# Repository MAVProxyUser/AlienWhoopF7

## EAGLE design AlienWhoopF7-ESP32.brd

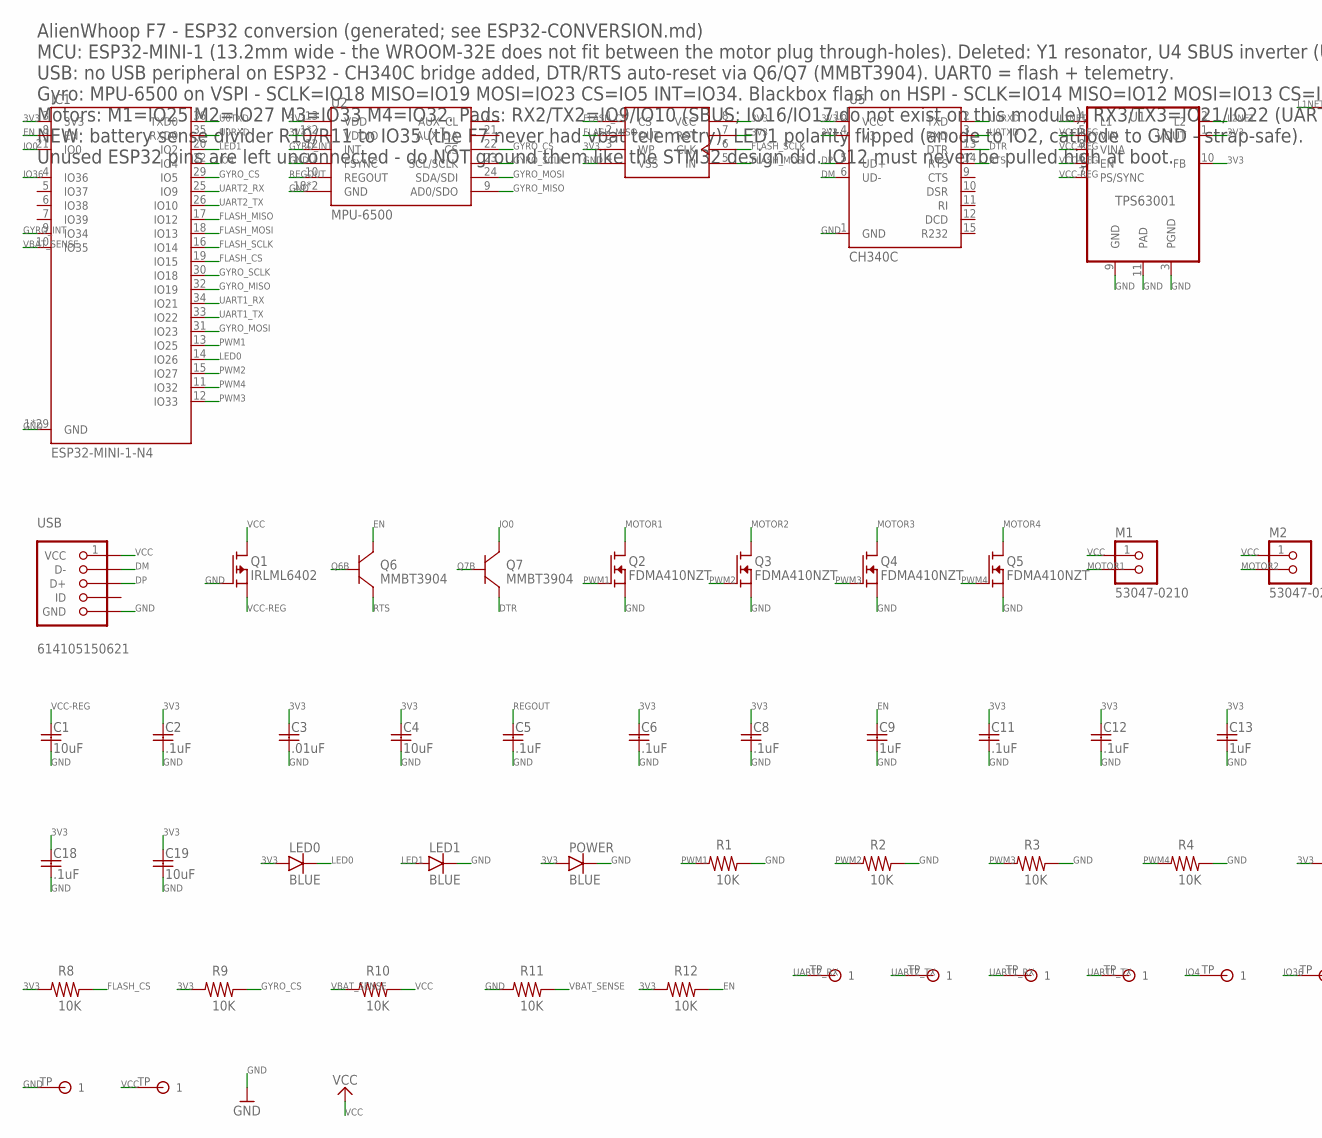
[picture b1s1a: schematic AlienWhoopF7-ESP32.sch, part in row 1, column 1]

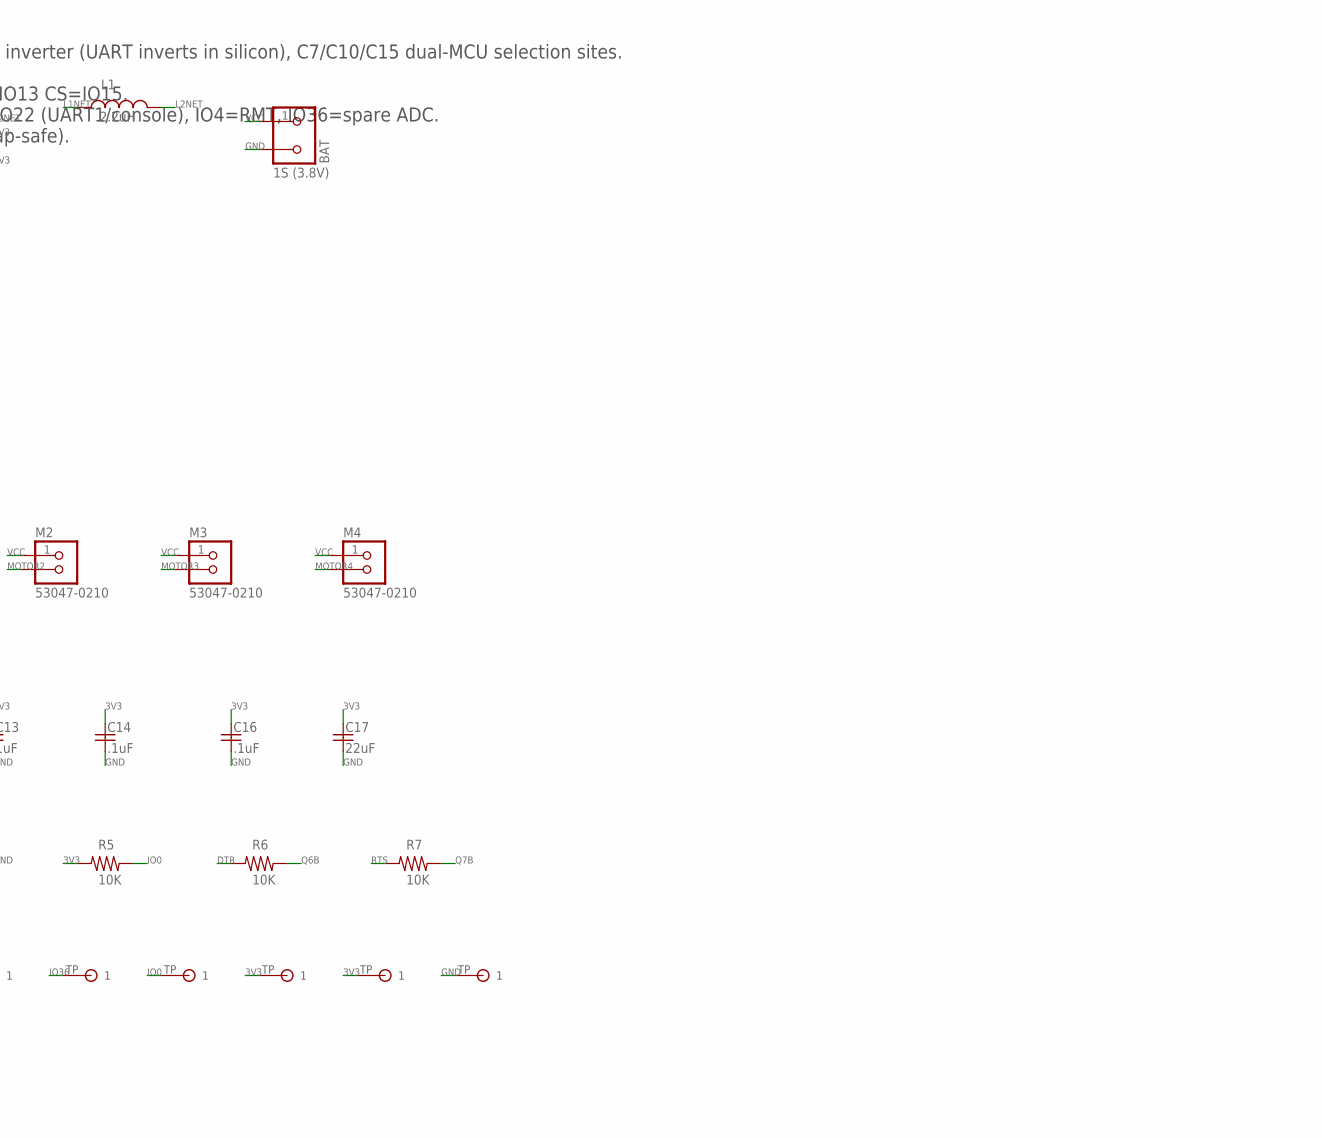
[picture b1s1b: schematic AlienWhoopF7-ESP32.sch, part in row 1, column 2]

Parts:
3.3V, 3V3: TESTPAD
BAT: 1S (3.8V); S2B-PH-K-S
BOOT: TESTPAD
C1, C4, C19: 10uF; YUDEN-CAP-0805
C2, C5, C6, C8, C11, C12, C14, C16, C18: .1uF; MUR-CAP-0603
C3: .01uF; MUR-CAP-0603
C9, C13: 1uF; MUR-CAP-0603
C17: 22uF; YUDEN-CAP-0805
GND: TESTPAD
GND@1: TESTPAD
IC1: ESP32-MINI-1-N4; ESP32-MINI-1
IO4, IO36: TESTPAD
L1: 2.2uH; DFE201612E-2R2M-P2
LED0, LED1: BLUE; SMD-CHIP-LED-0805
M1, M2, M3, M4: 53047-0210; PICO-53047-02
POWER: BLUE; SMD-CHIP-LED-0805
Q1: IRLML6402; SOT-23
Q2, Q3, Q4, Q5: FDMA410NZT; MICROFET-2X2
Q6, Q7: MMBT3904; SOT23
R1, R2, R3, R4, R5, R6, R7, R8, R9, R10, R11, R12: 10K; VISH-RES-0603
RX2, RX3: TESTPAD
TX2, TX3: TESTPAD
U1: TPS63001; VSON-N10
U2: MPU-6500; QFN24_PAD
U3: MX25L6406EM2I-12G; M25P32
U5: CH340C; SOP16
USB: 614105150621; USB-BFPV
VCC@1: TESTPAD

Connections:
3V3: 3.3V.TP, 3V3.TP, C2.1, C3.1, C4.1, C6.1, C8.1, C11.1, C12.1, C13.1, C14.1, C16.1, C17.1, C18.1, C19.1, IC1.3 (3V3), LED0.A, POWER.A, R5.2, R8.2, R9.2, R12.2, U1.1 (VOUT), U1.10 (FB), U2.1 (VDDIO), U2.8 (VDDIO), U2.13 (VDD), U3.3 (WP), U3.7 (RST), U3.8 (VCC), U5.4 (V3), U5.16 (VCC)
DM: U5.6 (UD-), USB.2 (D-)
DP: U5.5 (UD+), USB.3 (D+)
DTR: Q7.2 (E), R6.2, U5.13 (DTR)
EN: C9.1, IC1.8 (EN), Q6.3 (C), R12.1
FLASH_CS: IC1.19 (IO15), R8.1, U3.1 (CS)
FLASH_MISO: IC1.17 (IO12), U3.2 (OUT)
FLASH_MOSI: IC1.18 (IO13), U3.5 (IN)
FLASH_SCLK: IC1.16 (IO14), U3.6 (CLK)
GND: BAT.2, C1.2, C2.2, C3.2, C4.2, C5.2, C6.2, C8.2, C9.2, C11.2, C12.2, C13.2, C14.2, C16.2, C17.2, C18.2, C19.2, GND.TP, GND@1.TP, IC1.1 (GND), IC1.2 (GND), IC1.27 (GND), IC1.38 (GND), IC1.39 (GND), IC1.40 (GND), IC1.41 (GND), IC1.42 (GND), IC1.43 (GND), IC1.44 (GND), IC1.45 (GND), IC1.46 (GND), IC1.47 (GND), IC1.48 (GND), IC1.49 (GND), IC1.50 (GND), IC1.51 (GND), IC1.52 (GND), IC1.53 (GND), IC1.54 (GND), IC1.55 (GND), IC1.T1 (GND), IC1.T2 (GND), IC1.T3 (GND), IC1.T4 (GND), IC1.T5 (GND), IC1.T6 (GND), IC1.T7 (GND), IC1.T8 (GND), LED1.C, POWER.C, Q1.1 (G), Q2.S, Q2.S1 (S), Q3.S, Q3.S1 (S), Q4.S, Q4.S1 (S), Q5.S, Q5.S1 (S), R1.1, R2.1, R3.1, R4.1, R11.2, U1.3 (PGND), U1.9 (GND), U1.11 (PAD), U2.11 (FSYNC), U2.18 (GND), U2.20 (GND), U3.4 (VSS), U5.1 (GND), USB.5 (GND), USB.P$6 (GND), USB.P$7 (GND)
GYRO_CS: IC1.29 (IO5), R9.1, U2.22 (!CS)
GYRO_INT: IC1.9 (IO34), U2.12 (INT)
GYRO_MISO: IC1.32 (IO19), U2.9 (AD0/SDO)
GYRO_MOSI: IC1.31 (IO23), U2.24 (SDA/SDI)
GYRO_SCLK: IC1.30 (IO18), U2.23 (SCL/SCLK)
IO0: BOOT.TP, IC1.21 (IO0), Q7.3 (C), R5.1
IO4: IC1.22 (IO4), IO4.TP
IO36: IC1.4 (IO36), IO36.TP
L1NET: L1.P$1 (1), U1.4 (L1)
L2NET: L1.P$2 (2), U1.2 (L2)
LED0: IC1.14 (IO26), LED0.C
LED1: IC1.20 (IO2), LED1.A
MOTOR1: M1.2, Q2.D, Q2.D1 (D), Q2.D2 (D), Q2.D3 (D), Q2.D4 (D)
MOTOR2: M2.2, Q3.D, Q3.D1 (D), Q3.D2 (D), Q3.D3 (D), Q3.D4 (D)
MOTOR3: M3.2, Q4.D, Q4.D1 (D), Q4.D2 (D), Q4.D3 (D), Q4.D4 (D)
MOTOR4: M4.2, Q5.D, Q5.D1 (D), Q5.D2 (D), Q5.D3 (D), Q5.D4 (D)
PWM1: IC1.13 (IO25), Q2.G, R1.2
PWM2: IC1.15 (IO27), Q3.G, R2.2
PWM3: IC1.12 (IO33), Q4.G, R3.2
PWM4: IC1.11 (IO32), Q5.G, R4.2
Q6B: Q6.1 (B), R6.1
Q7B: Q7.1 (B), R7.1
REGOUT: C5.1, U2.10 (REGOUT)
RTS: Q6.2 (E), R7.2, U5.14 (RTS)
U0RXD: IC1.35 (RXD0), U5.2 (TXD)
U0TXD: IC1.36 (TXD0), U5.3 (RXD)
UART1_RX: IC1.34 (IO21), RX3.TP
UART1_TX: IC1.33 (IO22), TX3.TP
UART2_RX: IC1.25 (IO9), RX2.TP
UART2_TX: IC1.26 (IO10), TX2.TP
VBAT_SENSE: IC1.10 (IO35), R10.2, R11.1
VCC: BAT.1, M1.1, M2.1, M3.1, M4.1, Q1.3 (D), R10.1, USB.1 (VCC), VCC@1.TP
VCC-REG: C1.1, Q1.2 (S), U1.5 (VIN), U1.6 (EN), U1.7 (PS/SYNC), U1.8 (VINA)

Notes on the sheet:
AlienWhoop F7 - ESP32 conversion (generated; see ESP32-CONVERSION.md)
MCU: ESP32-MINI-1 (13.2mm wide - the WROOM-32E does not fit between the motor plug through-holes). Deleted: Y1 resonator, U4 SBUS inverter (UART inverts in silicon), C7/C10/C15 dual-MCU selection sites.
USB: no USB peripheral on ESP32 - CH340C bridge added, DTR/RTS auto-reset via Q6/Q7 (MMBT3904). UART0 = flash + telemetry.
Gyro: MPU-6500 on VSPI - SCLK=IO18 MISO=IO19 MOSI=IO23 CS=IO5 INT=IO34. Blackbox flash on HSPI - SCLK=IO14 MISO=IO12 MOSI=IO13 CS=IO15.
Motors: M1=IO25 M2=IO27 M3=IO33 M4=IO32. Pads: RX2/TX2=IO9/IO10 (SBUS; IO16/IO17 do not exist on this module), RX3/TX3=IO21/IO22 (UART1/console), IO4=RMT, IO36=spare ADC.
NEW: battery sense divider R10/R11 to IO35 (the F7 never had vbat telemetry). LED1 polarity flipped (anode to IO2, cathode to GND - strap-safe).
Unused ESP32 pins are left unconnected - do NOT ground them like the STM32 design did. IO12 must never be pulled high at boot.

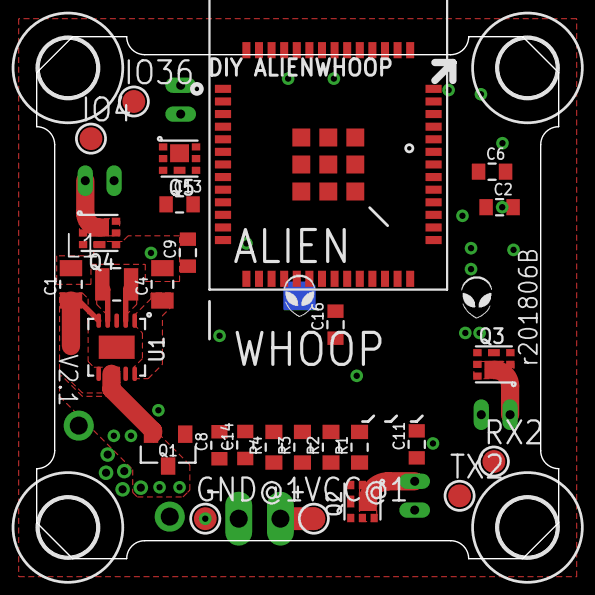
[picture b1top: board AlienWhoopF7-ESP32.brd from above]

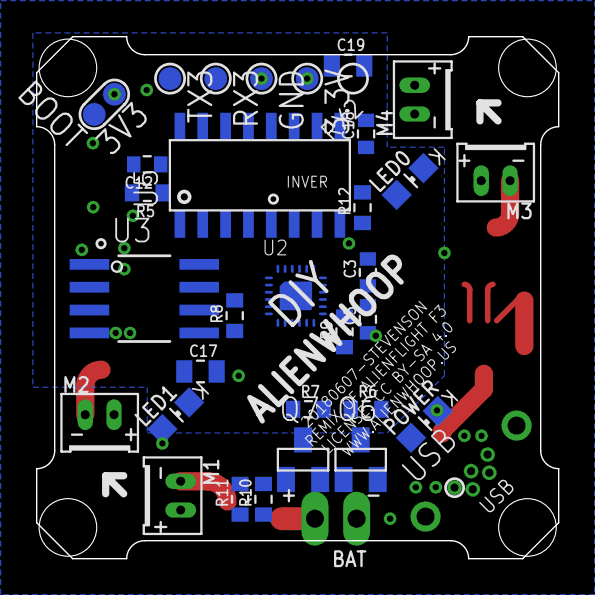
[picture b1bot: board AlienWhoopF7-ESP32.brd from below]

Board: 2 copper layers, 29.0 x 29.0 mm, 66 parts (34 on the bottom side), 43 nets.

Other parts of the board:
U$1, U$2, U$3, U$4: 3,2

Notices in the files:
AlienWhoopF7-ESP32.brd:
Released under the Creative Commons Attribution-ShareAlike 4.0 International License
https://creativecommons.org/licenses/by-sa/4.0
LICENSE: CC BY-SA 4.0
parts and their libraries:
SparkFun-Aesthetics: Licensing: Creative Commons ShareAlike 4.0 International - https://creativecommons.org/licenses/by-sa/4.0
alienflight: License: CC BY SA
alienflight: Released under the Creative Commons
Attribution Share-Alike 4.0 License
http://creativecommons.org/licenses/by-sa/4.0
